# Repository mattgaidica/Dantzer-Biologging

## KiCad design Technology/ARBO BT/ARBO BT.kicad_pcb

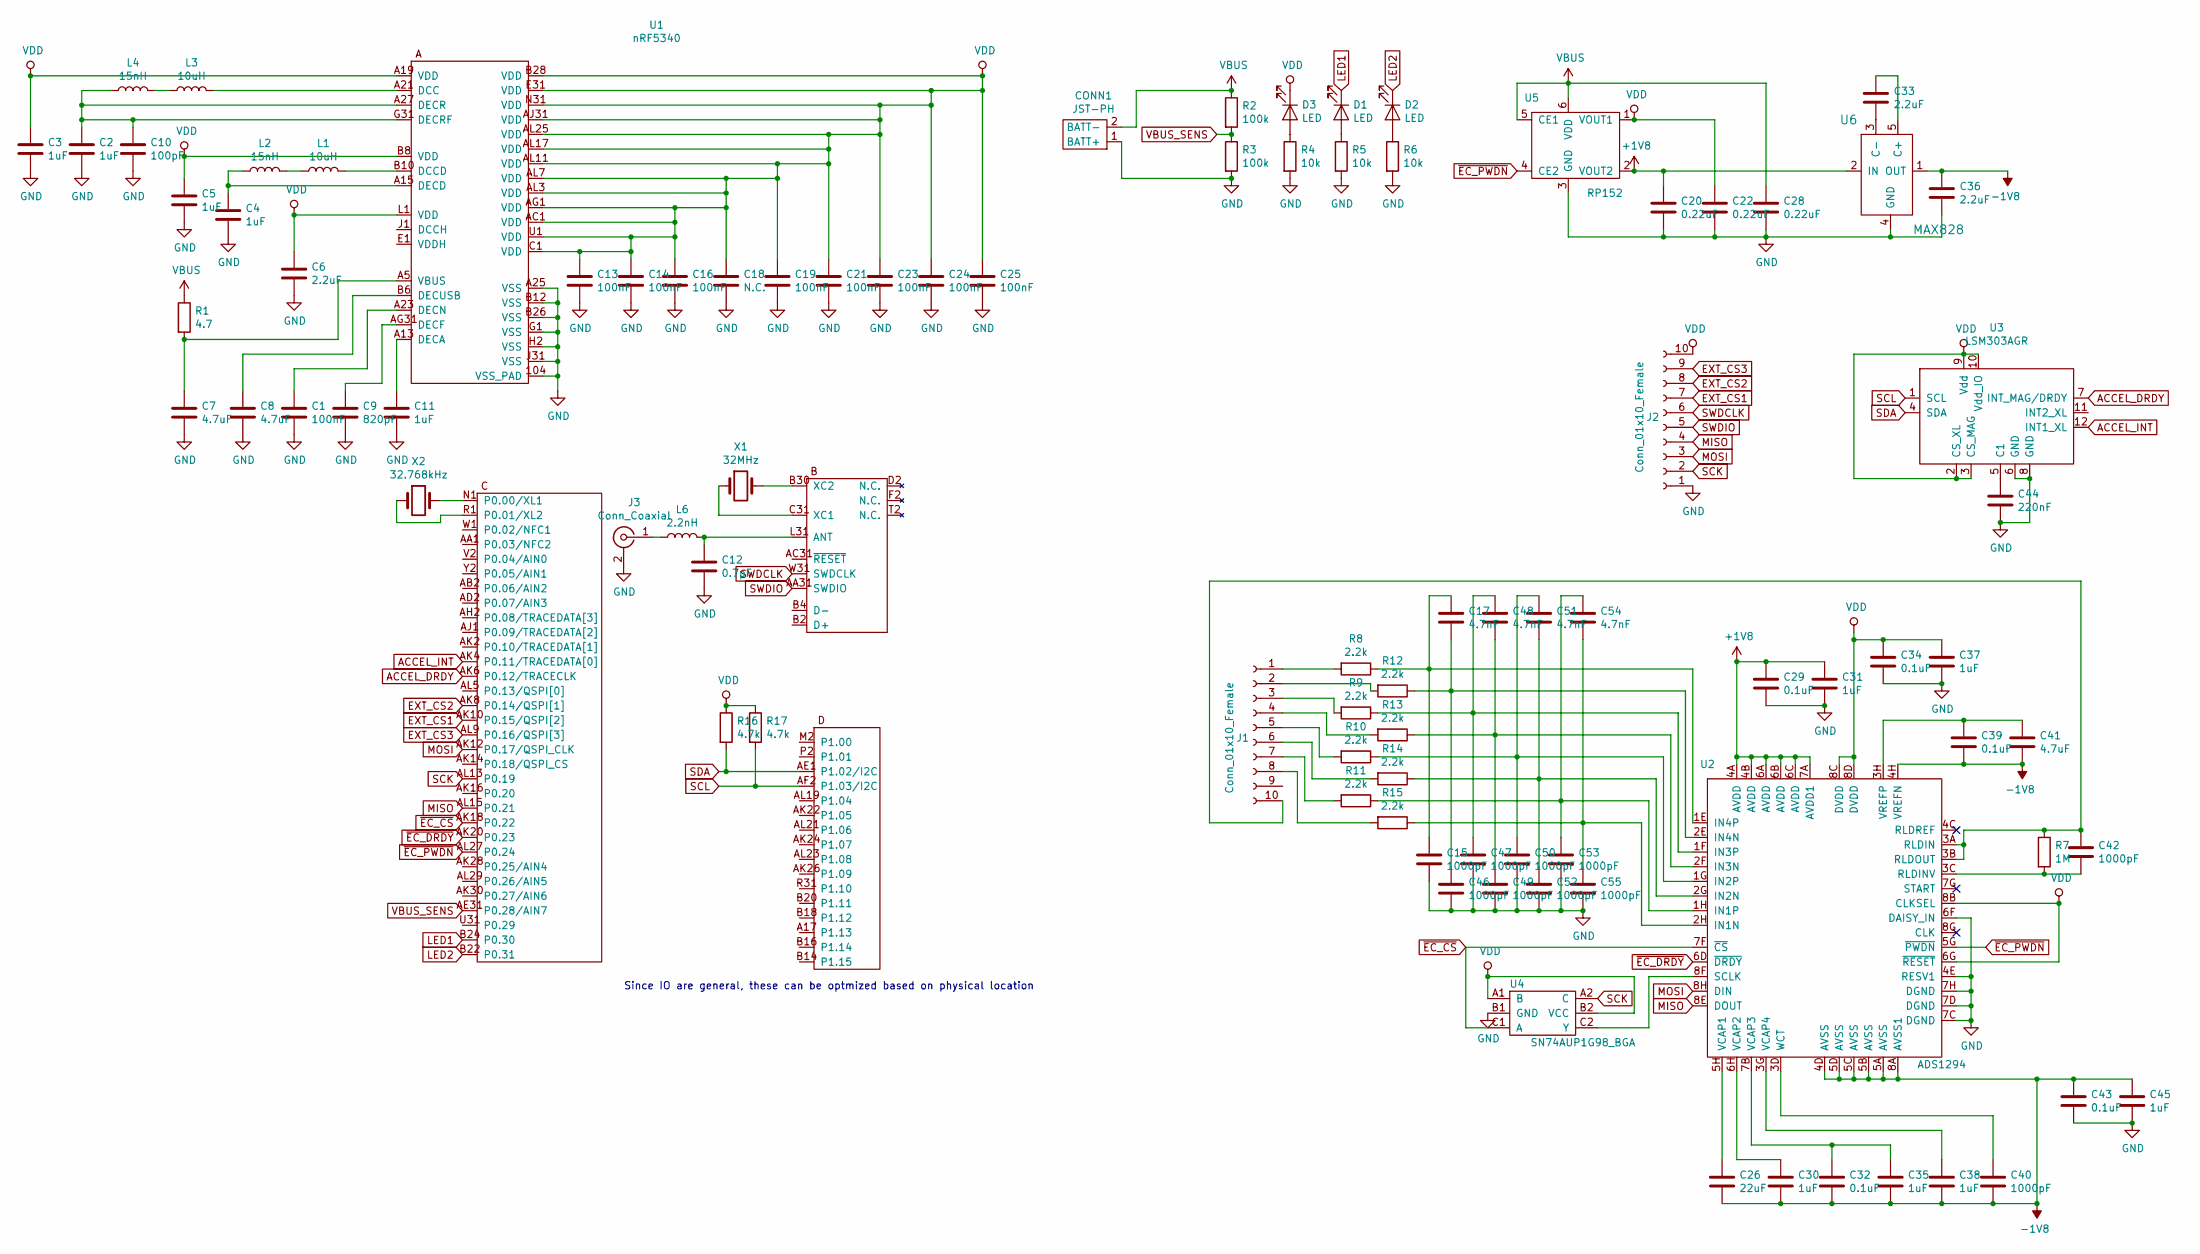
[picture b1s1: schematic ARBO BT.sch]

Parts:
C1, C13, C14, C16, C19, C21, C23, C24, C25: 100nF; C_0201_0603Metric
C2, C3, C4, C5, C11, C30, C31, C35, C37, C38, C45: 1uF; C_0402_1005Metric
C6, C33, C36: 2.2uF; C_0603_1608Metric
C7, C8, C41: 4.7uF; C_0603_1608Metric
C9: 820pF; C_0201_0603Metric
C10: 100pF; C_0201_0603Metric
C12: 0.7pF; C_0201_0603Metric
C15: 1000pF; C_0201_0603Metric
C17: 4.7nF; C_0201_0603Metric
C18: N.C.; C_0201_0603Metric
C20, C22, C28: 0.22uF; C_0402_1005Metric
C26: 22uF; C_0201_0603Metric
C29, C32, C34, C39, C43: 0.1uF; C_0201_0603Metric; digikey 490-16364-1-ND
C40, C42: 1000pF; C_0201_0603Metric; digikey 311-2073-1-ND
C44: 220nF; C_0402_1005Metric
C46, C47, C49, C50, C52, C53, C55: 1000pF; D_0201_0603Metric
C48, C51, C54: 4.7nF; D_0201_0603Metric
CONN1: JST-PH; JST_SHL_SM02B-SHLS-TF_1x02-1MP_P1.00mm_Horizontal
D1, D2, D3: LED; LED_0402_1005Metric
J1: Conn_01x10_Female; Hirose_DF52-10S-0.8H_1x10-1MP_P0.80mm_Horizontal
J2: Conn_01x10_Female; hirose_DF37NB-10
J3: Conn_Coaxial; U.FL_Hirose_U.FL-R-SMT-1_Vertical; digikey H9161CT-ND
L1, L3: 10uH; L_0603_1608Metric
L2, L4: 15nH; L_0201_0603Metric
L6: 2.2nH; L_0201_0603Metric
R1: 4.7; R_0201_0603Metric
R2, R3: 100k; R_0201_0603Metric
R4, R5, R6: 10k; R_0201_0603Metric
R7: 1M; R_0201_0603Metric
R8, R9, R10, R11, R12, R13, R14, R15: 2.2k; R_0201_0603Metric
R16, R17: 4.7k; R_0201_0603Metric
U1: nRF5340; aQFN94_7x7
U2: ADS1294; BGA-64_8x8_8.0x8.0mm_ADS129x
U3: LSM303AGR; LGA-12_2x2mm_P0.5mm
U4: SN74AUP1G98_BGA; BGA-6_04pitch
U5: RP152; digikey RP152L006B-TR
U6: MAX828; SOT-23-5
X1: 32MHz; Crystal_SMD_2016-4Pin_2.0x1.6mm
X2: 32.768kHz; Crystal_SMD_2012-2Pin_2.0x1.2mm

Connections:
+1V8: C20.1, C29.1, C31.1, U2.4A (AVDD), U2.4B (AVDD), U2.6A (AVDD), U2.6B (AVDD), U2.6C (AVDD), U2.7A (AVDD1), U5.2 (VOUT2), U6.2 (IN)
-1V8: C26.2, C30.2, C32.2, C35.2, C36.1, C38.2, C39.2, C40.2, C41.2, C43.1, C45.1, U2.4D (AVSS), U2.4H (VREFN), U2.5A (AVSS), U2.5B (AVSS), U2.5C (AVSS), U2.5D (AVSS), U2.8A (AVSS1), U6.1 (OUT)
ACCEL_DRDY: U1.AK6 (P0.12/TRACECLK), U3.7 (INT_MAG/DRDY)
ACCEL_INT: U1.AK4 (P0.11/TRACEDATA[0]), U3.12 (INT1_XL)
EXT_CS1: J2.7, U1.AK10 (P0.15/QSPI[2])
EXT_CS2: J2.8, U1.AK8 (P0.14/QSPI[1])
EXT_CS3: J2.9, U1.AL9 (P0.16/QSPI[3])
GND: C1.2, C2.2, C3.2, C4.2, C5.2, C6.2, C7.2, C8.2, C9.2, C10.2, C11.2, C12.2, C13.2, C14.2, C15.2, C16.2, C18.2, C19.2, C20.2, C21.2, C22.2, C23.2, C24.2, C25.2, C28.2, C29.2, C31.2, C34.2, C36.2, C37.2, C43.2, C44.2, C45.2, C46.2, C47.2, C49.2, C50.2, C52.2, C53.2, C55.2, CONN1.1 (BATT+), J2.1, J3.2 (Ext), R3.2, R4.2, R5.2, R6.2, U1.104 (VSS_PAD), U1.A25 (VSS), U1.B12 (VSS), U1.B26 (VSS), U1.G1 (VSS), U1.H2 (VSS), U1.J31 (VSS), U2.4E (RESV1), U2.6F (DAISY_IN), U2.7C (DGND), U2.7D (DGND), U2.7H (DGND), U3.6 (GND), U3.8 (GND), U4.B1 (GND), U5.3 (GND), U6.4 (GND)
LED1: D1.1 (K), U1.B24 (P0.30)
LED2: D2.1 (K), U1.B22 (P0.31)
MISO: J2.4, U1.AL15 (P0.21), U2.8E (DOUT)
MOSI: J2.3, U1.AK12 (P0.17/QSPI_CLK), U2.8H (DIN)
unnamed: C1.1, U1.A23 (DECN)
unnamed: C4.1, L2.1, U1.A15 (DECD)
unnamed: C7.1, R1.2, U1.A5 (VBUS)
unnamed: C8.1, U1.B6 (DECUSB)
unnamed: C9.1, U1.AG31 (DECF)
unnamed: C2.1, C10.1, L4.1, U1.A27 (DECR), U1.G31 (DECRF)
unnamed: C11.1, U1.A13 (DECA)
unnamed: C12.1, L6.2, U1.L31 (ANT)
unnamed: C15.1, C17.1, R8.1, U2.1E (IN4P)
unnamed: C17.2, C46.1, R12.1, U2.2E (IN4N)
unnamed: C26.1, U2.5H (VCAP1)
unnamed: C30.1, U2.6H (VCAP2)
unnamed: C32.1, C35.1, U2.7B (VCAP3)
unnamed: C33.1, U6.5 (C+)
unnamed: C33.2, U6.3 (C-)
unnamed: C38.1, U2.3G (VCAP4)
unnamed: C39.1, C41.1, U2.3H (VREFP)
unnamed: C40.1, U2.3D (WCT)
unnamed: C42.1, J1.10, R7.1, U2.3A (RLDIN), U2.3B (RLDOUT)
unnamed: C42.2, R7.2, U2.3C (RLDINV)
unnamed: C44.1, U3.5 (C1)
unnamed: C47.1, C48.1, R9.1, U2.1F (IN3P)
unnamed: C48.2, C49.1, R13.1, U2.2F (IN3N)
unnamed: C50.1, C51.1, R10.1, U2.1G (IN2P)
unnamed: C51.2, C52.1, R14.1, U2.2G (IN2N)
unnamed: C53.1, C54.1, R11.1, U2.1H (IN1P)
unnamed: C54.2, C55.1, R15.1, U2.2H (IN1N)
unnamed: D1.2 (A), R5.1
unnamed: D2.2 (A), R6.1
unnamed: D3.2 (A), R4.1
unnamed: J1.1, R8.2
unnamed: J1.2, R12.2
unnamed: J1.3, R9.2
unnamed: J1.4, R13.2
unnamed: J1.5, R10.2
unnamed: J1.6, R14.2
unnamed: J1.7, R11.2
unnamed: J1.8, R15.2
unnamed: J3.1 (In), L6.1
unnamed: L1.1, L2.2
unnamed: L1.2, U1.B10 (DCCD)
unnamed: L3.1, L4.2
unnamed: L3.2, U1.A21 (DCC)
unnamed: U1.B30 (XC2), X1.2
unnamed: U1.C31 (XC1), X1.1
unnamed: U1.N1 (P0.00/XL1), X2.2
unnamed: U1.R1 (P0.01/XL2), X2.1
unnamed: U2.8F (SCLK), U4.C2 (Y)
SCK: J2.2, U1.AL13 (P0.19), U4.A2 (C)
SCL: R17.2, U1.AF2 (P1.03/I2C), U3.1 (SCL)
SDA: R16.2, U1.AE1 (P1.02/I2C), U3.4 (SDA)
SWDCLK: J2.6, U1.W31 (SWDCLK)
SWDIO: J2.5, U1.AA31 (SWDIO)
VBUS: C28.1, CONN1.2 (BATT-), R1.1, R2.1, U5.5 (CE1), U5.6 (VDD)
VBUS_SENS: R2.2, R3.1, U1.AE31 (P0.28/AIN7)
VDD: C3.1, C5.1, C6.1, C13.1, C14.1, C16.1, C18.1, C19.1, C21.1, C22.1, C23.1, C24.1, C25.1, C34.1, C37.1, D3.1 (K), J2.10, R16.1, R17.1, U1.A19 (VDD), U1.AC1 (VDD), U1.AG1 (VDD), U1.AJ31 (VDD), U1.AL3 (VDD), U1.AL7 (VDD), U1.AL11 (VDD), U1.AL17 (VDD), U1.AL25 (VDD), U1.B8 (VDD), U1.B28 (VDD), U1.C1 (VDD), U1.E31 (VDD), U1.L1 (VDD), U1.N31 (VDD), U1.U1 (VDD), U2.6G (~RESET), U2.8B (CLKSEL), U2.8C (DVDD), U2.8D (DVDD), U3.2 (CS_XL), U3.3 (CS_MAG), U3.9 (Vdd), U3.10 (Vdd_IO), U4.A1 (B), U4.B2 (VCC), U5.1 (VOUT1)
~EC_CS: U1.AK18 (P0.22), U2.7F (~CS), U4.C1 (A)
~EC_DRDY: U1.AK20 (P0.23), U2.6D (~DRDY)
~EC_PWDN: U1.AL27 (P0.24), U2.5G (~PWDN), U5.4 (CE2)

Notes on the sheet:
Since IO are general, these can be optmized based on physical location

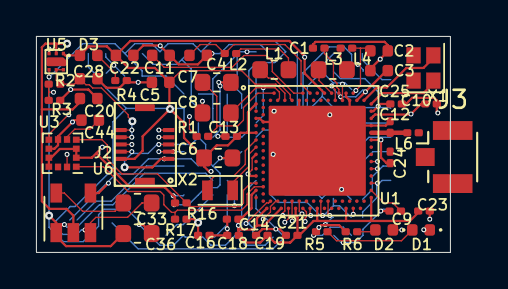
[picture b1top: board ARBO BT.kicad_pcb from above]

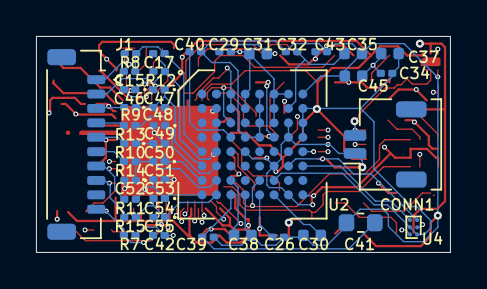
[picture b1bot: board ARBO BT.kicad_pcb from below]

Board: 4 copper layers, 23.0 x 12.0 mm, 91 parts (40 on the bottom side), 71 nets.

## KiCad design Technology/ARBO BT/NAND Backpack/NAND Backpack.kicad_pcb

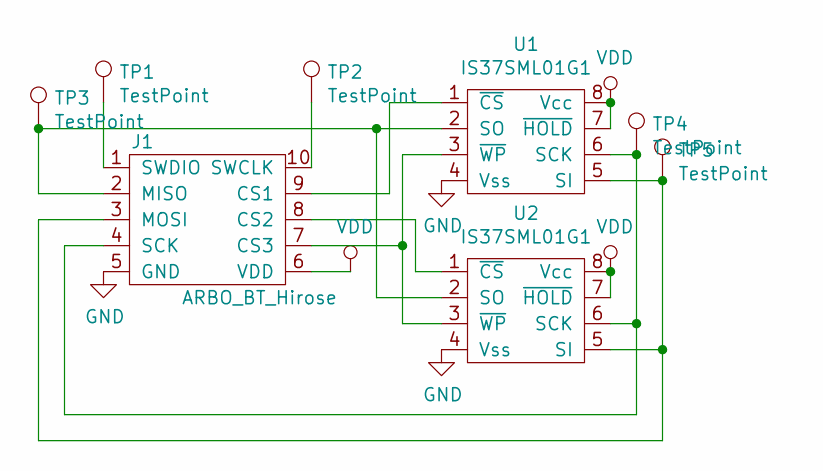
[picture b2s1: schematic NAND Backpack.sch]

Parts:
J1: ARBO_BT_Hirose; hirose_DF37B-10
TP1, TP2, TP3, TP4, TP5: TestPoint; TestPoint_Pad_D1.0mm
U1, U2: IS37SML01G1; 8x6mm_WSON_UTSO

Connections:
GND: J1.5 (GND), U1.4 (Vss), U2.4 (Vss)
unnamed: J1.1 (SWDIO), TP1.1
unnamed: J1.2 (MISO), TP3.1, U1.2 (SO), U2.2 (SO)
unnamed: J1.3 (MOSI), TP5.1, U1.5 (SI), U2.5 (SI)
unnamed: J1.4 (SCK), TP4.1, U1.6 (SCK), U2.6 (SCK)
unnamed: J1.7 (CS3), U1.3 (~WP), U2.3 (~WP)
unnamed: J1.8 (CS2), U2.1 (~CS)
unnamed: J1.9 (CS1), U1.1 (~CS)
unnamed: J1.10 (SWCLK), TP2.1
VDD: J1.6 (VDD), U1.7 (~HOLD), U1.8 (Vcc), U2.7 (~HOLD), U2.8 (Vcc)

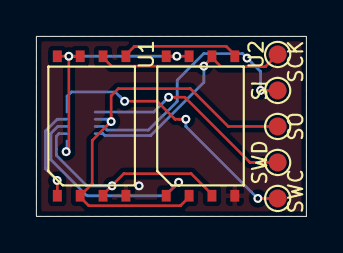
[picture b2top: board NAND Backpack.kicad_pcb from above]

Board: 2 copper layers, 15.0 x 10.0 mm, 8 parts (1 on the bottom side), 10 nets.

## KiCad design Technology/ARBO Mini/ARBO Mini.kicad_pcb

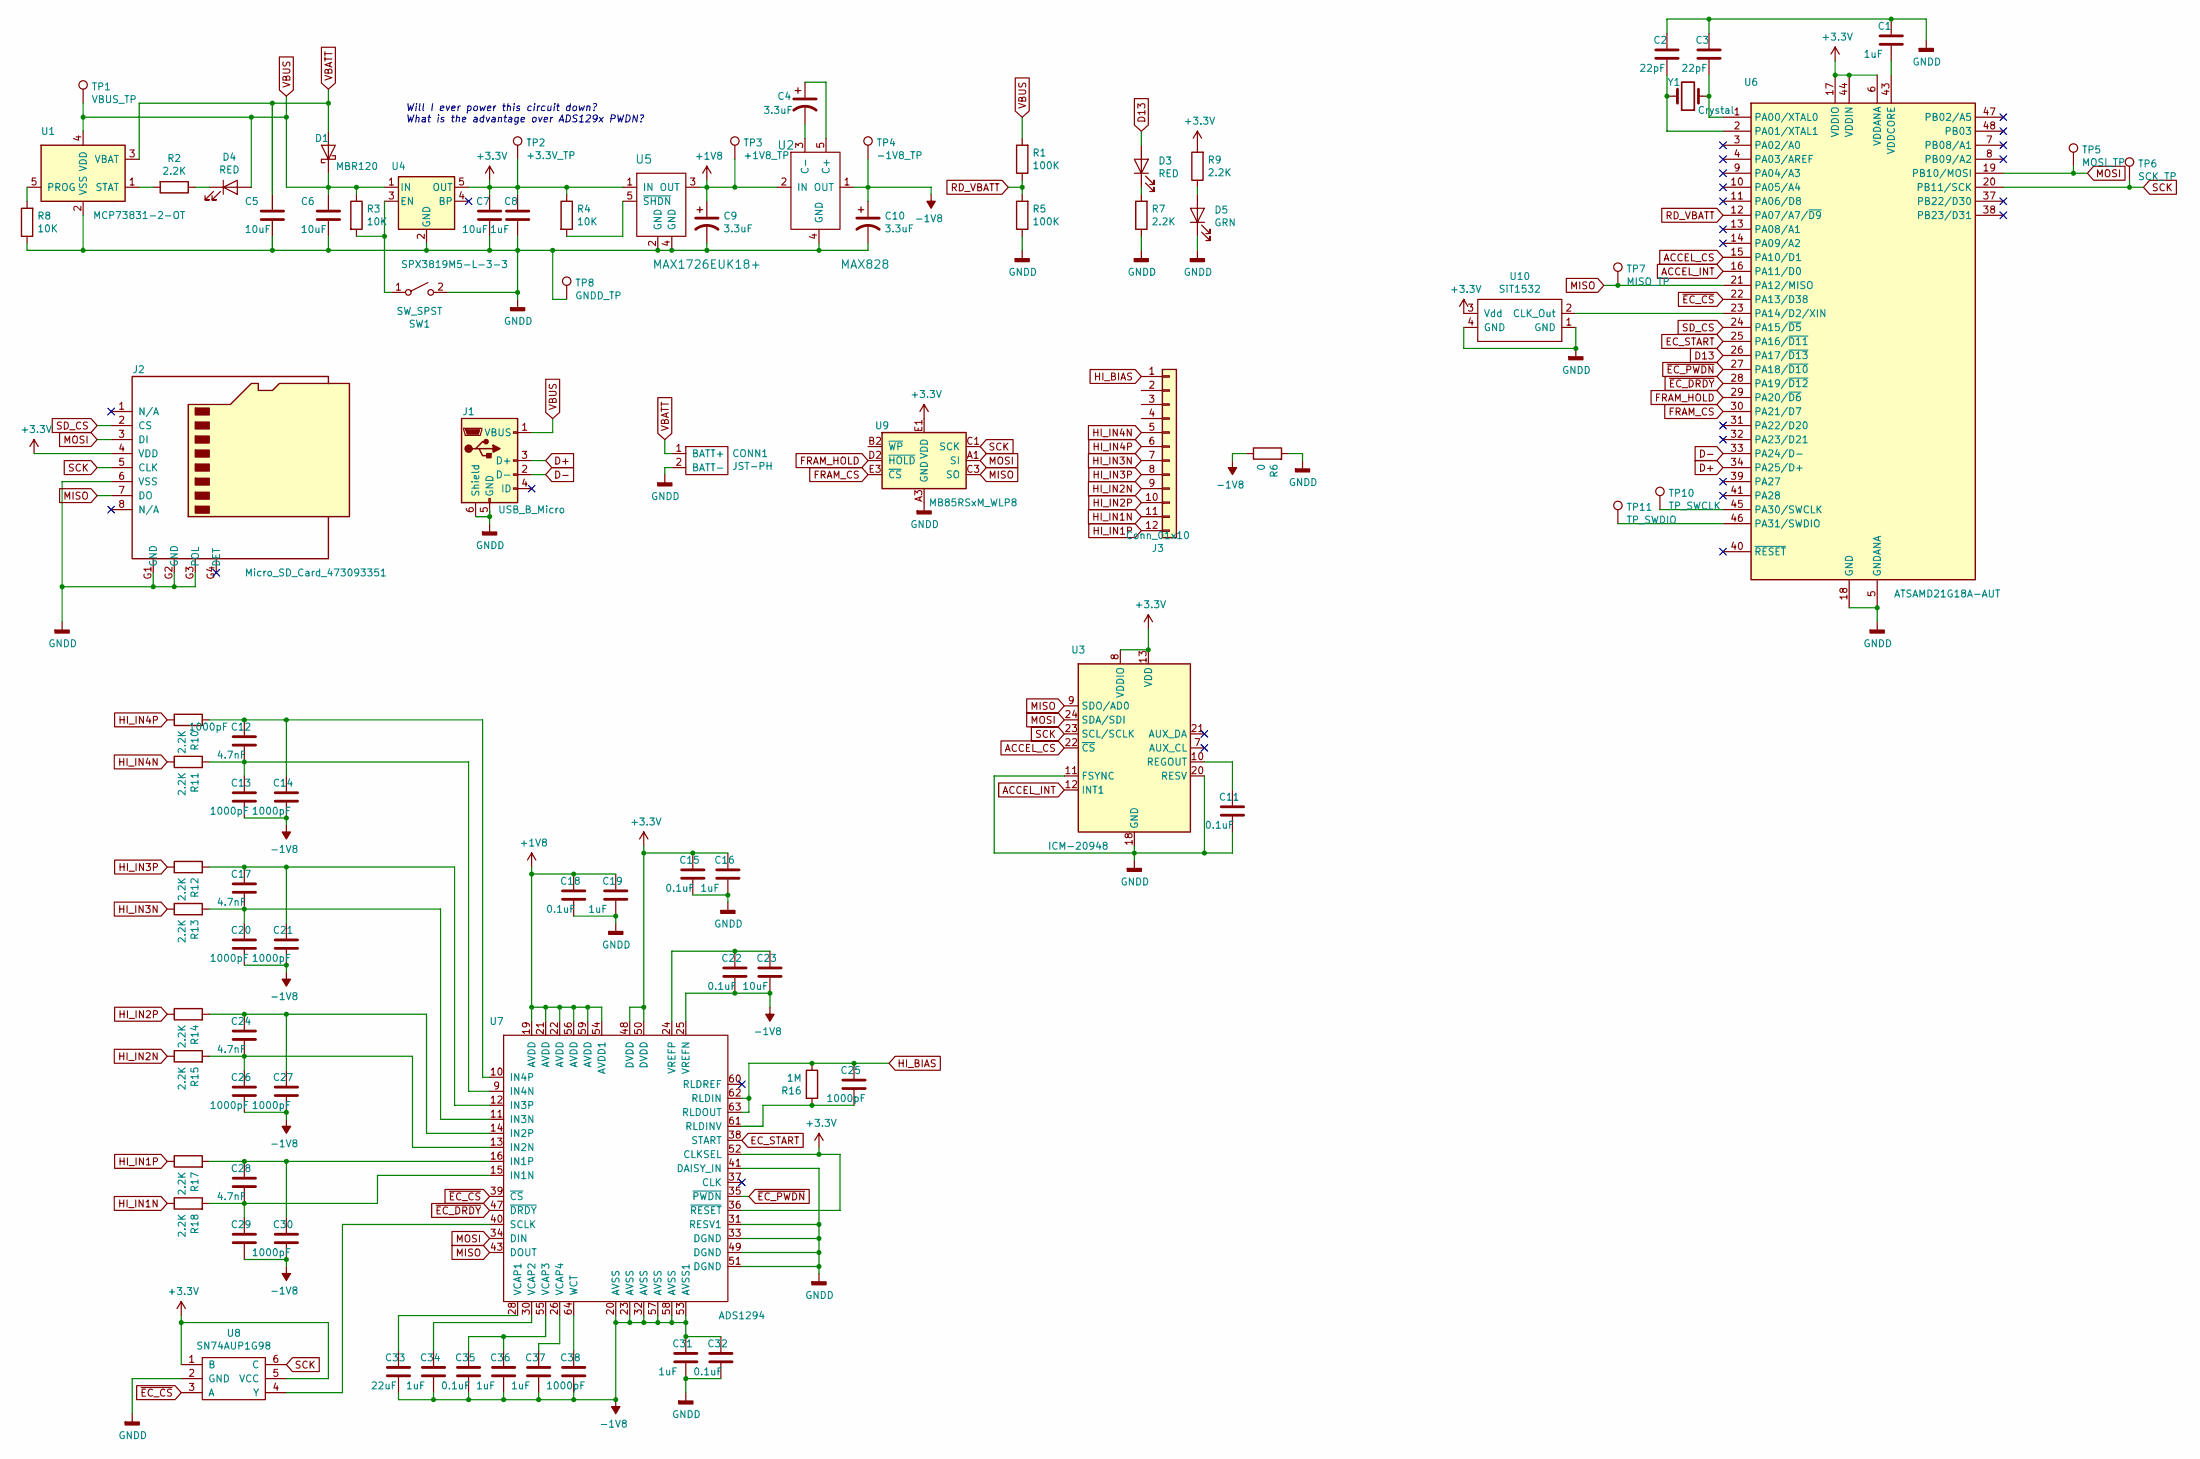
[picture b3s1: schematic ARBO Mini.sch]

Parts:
C1, C8, C16, C31, C34, C36, C37: 1uF; C_0402_1005Metric; Manufacturer Part Number C0402C105K9PACTU; Digi-key Part Number 399-4873-1-ND
C2, C3: 22pF; C_0402_1005Metric; Manufacturer Part Number C0402C220K5GACTU; Digi-key Part Number 399-7775-1-ND
C4, C9, C10: 3.3uF; C_0402_1005Metric; Manufacturer Part Number C1005X5R0G335K050BB; Digi-key Part Number 445-5948-1-ND
C5, C6, C7, C23: 10uF; C_0603_1608Metric; Manufacturer Part Number GRM155R60E106ME16D; Digi-key Part Number 490-10692-1-ND
C11, C15, C18, C22, C32, C35: 0.1uF; C_0402_1005Metric; Manufacturer Part Number LMK105BJ104KV-F; Digi-key Part Number 587-1227-1-ND
C12, C17, C24, C28: 4.7nF; C_0402_1005Metric; Manufacturer Part Number C0402C472K4RECAUTO; Digi-key Part Number 399-17875-1-ND
C13, C14, C20, C21, C25, C26, C27, C29, C30, C38: 1000pF; C_0402_1005Metric; Manufacturer Part Number GRM1555C1H102JA01J; Digi-key Part Number 490-6190-1-ND
C19: 1uF; C_0402_1005Metric; Manufacturer Part Number LMK105BJ104KV-F; Digi-key Part Number 587-1227-1-ND
C33: 22uF; C_0603_1608Metric; Manufacturer Part Number GRM188R60J226MEA0D; Digi-key Part Number 490-7611-1-ND
CONN1: JST-PH; PinHeader_1x02_P2.00mm_Horizontal
D1: MBR120; D_SOD-123F; Manufacturer Part Number MBR120VLSFT1G; Digi-key Part Number MBR120VLSFT1GOSCT-ND
D3, D4: RED; LED_0402_1005Metric; Manufacturer Part Number 150040RS73240; Digi-key Part Number 732-11991-1-ND
D5: GRN; LED_0402_1005Metric; Manufacturer Part Number 150040VS73240; Digi-key Part Number 732-11992-1-ND
J1: USB_B_Micro; USB_Micro-B_Molex-105017-0001; Manufacturer Part Number 1050170001; Digi-key Part Number WM1399CT-ND
J2: Micro_SD_Card_473093351; 473093351_uSDCard; Manufacturer Part Number 0473093351; Digi-key Part Number WM10795CT-ND
J3: Conn_01x10; Hirose_DF52-12S-0.8H_1x12-1MP_P0.80mm_Horizontal; Manufacturer Part Number DF52-12S-0.8H(21); Digi-key Part Number H125103CT-ND
R1, R5: 100K; R_0402_1005Metric; Manufacturer Part Number RC0402FR-07100KL; Digi-key Part Number 311-100KLRCT-ND
R2, R7, R9, R10, R11, R12, R13, R14, R15, R17, R18: 2.2K; R_0402_1005Metric; Manufacturer Part Number RC0402FR-072K2L; Digi-key Part Number 311-2.20KLRCT-ND
R3, R4, R8: 10K; R_0402_1005Metric; Manufacturer Part Number RC0402FR-0710KL; Digi-key Part Number 311-10.0KLRCT-ND
R6: 0; R_0402_1005Metric; Manufacturer Part Number RC0402JR-070RL; Digi-key Part Number 311-0.0JRCT-ND
R16: 1M; R_0402_1005Metric; Manufacturer Part Number RC0402FR-071ML; Digi-key Part Number 311-1.00MLRCT-ND
SW1: SW_SPST; SW_SPST_CK_KXT3; Manufacturer Part Number KXT 331 LHS; Digi-key Part Number CKN10779CT-ND
TP1: VBUS_TP; TestPoint_Pad_D1.5mm
TP2: +3.3V_TP; TestPoint_Pad_D1.5mm
TP3: +1V8_TP; TestPoint_Pad_D1.5mm
TP4: -1V8_TP; TestPoint_Pad_D1.5mm
TP5: MOSI_TP; TestPoint_Pad_D1.5mm
TP6: SCK_TP; TestPoint_Pad_D1.5mm
TP7: MISO_TP; TestPoint_Pad_D1.5mm
TP8: GNDD_TP; TestPoint_Pad_D1.5mm
TP10: TP_SWCLK; TestPoint_Pad_D1.5mm
TP11: TP_SWDIO; TestPoint_Pad_D1.5mm
U1: MCP73831-2-OT; SOT-23-5; Manufacturer Part Number MCP73831T-2ATI/OT; Digi-key Part Number MCP73831T-2ATI/OTCT-ND
U2: MAX828; SOT-23-5; Manufacturer Part Number MAX828EUK+T; Digi-key Part Number MAX828EUK+TCT-ND
U3: ICM-20948; InvenSense_QFN-24_3x3mm_P0.4mm; Manufacturer Part Number ICM-20948; Digi-key Part Number 1428-1123-1-ND
U4: SPX3819M5-L-3-3; SOT-23-5; Manufacturer Part Number SPX3819M5-L-3-3/TR; Digi-key Part Number 1016-1873-1-ND
U5: MAX1726EUK18+; SOT-23-5; Manufacturer Part Number MAX1726EUK18+T; Digi-key Part Number MAX1726EUK18+T-ND
U6: ATSAMD21G18A-AUT; QFN-48-1EP_7x7mm_P0.5mm_EP5.15x5.15mm; Manufacturer Part Number ATSAMD21G18A-MUT; Digi-key Part Number ATSAMD21G18A-MUTCT-ND
U7: ADS1294; TQFP-64-1EP_10x10mm_P0.5mm_EP8x8mm; Manufacturer Part Number ADS1294IPAG; Digi-key Part Number 296-27932-ND
U8: SN74AUP1G98; SOT-23-6; Manufacturer Part Number SN74AUP1G98DBVR; Digi-key Part Number 296-19087-1-ND
U9: MB85RSxM_WLP8; BGA8CP30X40_5X3_309X228X35B25N; Manufacturer Part Number MB85RS1MTPW-G-APEWE1; Digi-key Part Number 865-1272-2-ND
U10: SiT1532; Manufacturer Part Number SIT1532AI-J4-DCC-32.768E; Digi-key Part Number 1473-1240-1-ND
Y1: Crystal; Crystal_SMD_3215-2Pin_3.2x1.5mm; Manufacturer Part Number FC-135 32.7680KA-A5; Digi-key Part Number SER4103CT-ND

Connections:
+1V8: C9.1, C18.1, C19.1, TP3.1, U2.2 (IN), U5.3 (OUT), U7.19 (AVDD), U7.21 (AVDD), U7.22 (AVDD), U7.54 (AVDD1), U7.56 (AVDD), U7.59 (AVDD)
+3V3: C7.1, C8.1, C15.1, C16.1, J2.4 (VDD), R4.1, R9.2, TP2.1, U3.8 (VDDIO), U3.13 (VDD), U4.5 (OUT), U5.1 (IN), U6.6 (VDDANA), U6.17 (VDDIO), U6.36 (VDDIO), U6.44 (VDDIN), U7.36 (~RESET), U7.48 (DVDD), U7.50 (DVDD), U7.52 (CLKSEL), U8.1 (B), U8.5 (VCC), U9.E1 (VDD), U10.3 (Vdd)
-1V8: C10.1, C13.2, C14.2, C20.2, C21.2, C22.2, C23.2, C26.2, C27.2, C29.2, C30.2, C31.1, C32.1, C33.2, C34.2, C35.2, C36.2, C37.2, C38.2, R6.1, TP4.1, U2.1 (OUT), U7.20 (AVSS), U7.23 (AVSS), U7.25 (VREFN), U7.32 (AVSS), U7.53 (AVSS1), U7.57 (AVSS), U7.58 (AVSS)
ACCEL_CS: U3.22 (~CS), U6.15 (PA10/D1)
ACCEL_INT: U3.12 (INT1), U6.16 (PA11/D0)
D13: D3.2 (A), U6.26 (PA17/~D13)
D+: J1.3 (D+), U6.34 (PA25/D+)
D-: J1.2 (D-), U6.33 (PA24/D-)
EC_START: U6.25 (PA16/~D11), U7.38 (START)
FRAM_CS: U6.30 (PA21/D7), U9.E3 (~CS)
FRAM_HOLD: U6.29 (PA20/~D6), U9.D2 (~HOLD)
GNDD: C1.1, C2.1, C3.1, C5.2, C6.2, C7.2, C8.2, C9.2, C10.2, C11.2, C15.2, C16.2, C18.2, C19.2, C31.2, C32.2, CONN1.2 (BATT-), D5.1 (K), J1.5 (GND), J1.6 (Shield), J2.6 (VSS), J2.G1 (GND), J2.G2 (GND), J2.G3 (POL), R5.1, R6.2, R7.1, R8.1, SW1.2 (B), TP8.1, U1.2 (VSS), U2.4 (GND), U3.11 (FSYNC), U3.18 (GND), U3.20 (GND), U4.2 (GND), U5.2 (GND), U5.4 (GND), U6.5 (GNDANA), U6.18 (GND), U6.35 (GND), U6.42 (GND), U7.31 (RESV1), U7.33 (DGND), U7.41 (DAISY_IN), U7.49 (DGND), U7.51 (DGND), U8.2 (GND), U9.A3 (GND), U10.1 (GND), U10.4 (GND)
HI_BIAS: C25.1, J3.1, R16.1, U7.62 (RLDIN), U7.63 (RLDOUT)
HI_IN1N: J3.11, R18.1
HI_IN1P: J3.12, R17.1
HI_IN2N: J3.9, R15.1
HI_IN2P: J3.10, R14.1
HI_IN3N: J3.7, R13.1
HI_IN3P: J3.8, R12.1
HI_IN4N: J3.5, R11.1
HI_IN4P: J3.6, R10.1
MISO: J2.7 (DO), TP7.1, U3.9 (SDO/AD0), U6.21 (PA12/MISO), U7.43 (DOUT), U9.C3 (SO)
MOSI: J2.3 (DI), TP5.1, U3.24 (SDA/SDI), U6.19 (PB10/MOSI), U7.34 (DIN), U9.A1 (SI)
unnamed: C1.2, U6.43 (VDDCORE)
unnamed: C2.2, U6.2 (PA01/XTAL1), Y1.2
unnamed: C3.2, U6.1 (PA00/XTAL0), Y1.1
unnamed: C4.1, U2.5 (C+)
unnamed: C4.2, U2.3 (C-)
unnamed: C11.1, U3.10 (REGOUT)
unnamed: C12.1, C14.1, R10.2, U7.10 (IN4P)
unnamed: C12.2, C13.1, R11.2, U7.9 (IN4N)
unnamed: C17.1, C21.1, R12.2, U7.12 (IN3P)
unnamed: C17.2, C20.1, R13.2, U7.11 (IN3N)
unnamed: C22.1, C23.1, U7.24 (VREFP)
unnamed: C24.1, C27.1, R14.2, U7.14 (IN2P)
unnamed: C24.2, C26.1, R15.2, U7.13 (IN2N)
unnamed: C25.2, R16.2, U7.61 (RLDINV)
unnamed: C28.1, C30.1, R17.2, U7.16 (IN1P)
unnamed: C28.2, C29.1, R18.2, U7.15 (IN1N)
unnamed: C33.1, U7.28 (VCAP1)
unnamed: C34.1, U7.30 (VCAP2)
unnamed: C35.1, C36.1, U7.55 (VCAP3)
unnamed: C37.1, U7.26 (VCAP4)
unnamed: C38.1, U7.64 (WCT)
unnamed: D3.1 (K), R7.2
unnamed: D4.1 (K), R2.1
unnamed: D5.2 (A), R9.1
unnamed: R2.2, U1.1 (STAT)
unnamed: R3.2, SW1.1 (A), U4.3 (EN)
unnamed: R4.2, U5.5 (~SHDN)
unnamed: R8.2, U1.5 (PROG)
unnamed: TP10.1, U6.45 (PA30/SWCLK)
unnamed: TP11.1, U6.46 (PA31/SWDIO)
unnamed: U7.40 (SCLK), U8.4 (Y)
unnamed: U6.23 (PA14/D2/XIN), U10.2 (CLK_Out)
RD_VBATT: R1.1, R5.2, U6.12 (PA07/A7/~D9)
SCK: J2.5 (CLK), TP6.1, U3.23 (SCL/SCLK), U6.20 (PB11/SCK), U8.6 (C), U9.C1 (SCK)
SD_CS: J2.2 (CS), U6.24 (PA15/~D5)
VBATT: C5.1, CONN1.1 (BATT+), D1.2 (A), U1.3 (VBAT)
VBUS: C6.1, D1.1 (K), D4.2 (A), J1.1 (VBUS), R1.2, R3.1, TP1.1, U1.4 (VDD), U4.1 (IN)
~EC_CS: U6.22 (PA13/D38), U7.39 (~CS), U8.3 (A)
~EC_DRDY: U6.28 (PA19/~D12), U7.47 (~DRDY)
~EC_PWDN: U6.27 (PA18/~D10), U7.35 (~PWDN)

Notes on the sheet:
Will I ever power this circuit down? What is the advantage over ADS129x PWDN?

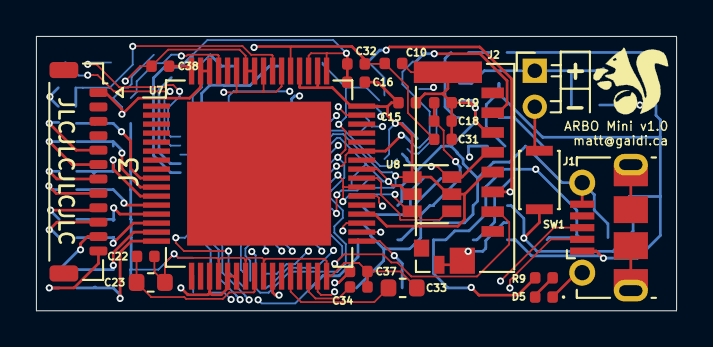
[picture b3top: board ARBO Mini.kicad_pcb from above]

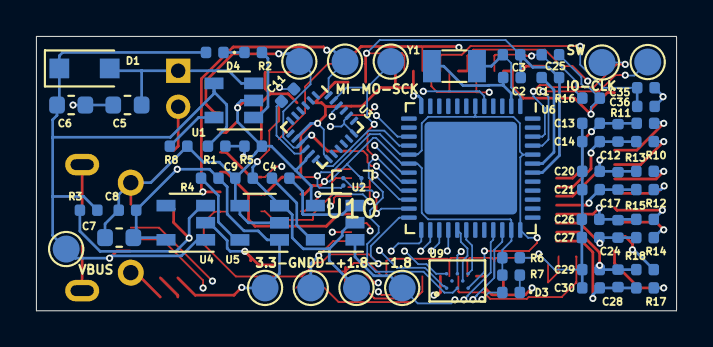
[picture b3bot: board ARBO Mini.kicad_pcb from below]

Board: 4 copper layers, 35.6 x 15.2 mm, 86 parts (64 on the bottom side), 63 nets.

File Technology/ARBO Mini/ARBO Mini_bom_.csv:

Component,Description,Part,References,Value,Footprint,Quantity Per PCB,Datasheet,Manufacturer Part Number,Digi-key Part Number,Link
1,Unpolarized capacitor,C,C11 C15 C18 C19 C22 C32 C35,0.1uF,C_0402_1005Metric,7,~,LMK105BJ104KV-F,587-1227-1-ND,
2,Unpolarized capacitor,C,C13 C14 C20 C21 C25 C26 C27 C29 C30 C38,1000pF,C_0402_1005Metric,10,~,GRM1555C1H102JA01J,490-6190-1-ND,
3,Unpolarized capacitor,C,C5 C6 C7 C23,10uF,C_0603_1608Metric,4,~,GRM155R60E106ME16D,490-10692-1-ND,
4,Unpolarized capacitor,C,C1 C8 C16 C31 C34 C36 C37,1uF,C_0402_1005Metric,7,~,C0402C105K9PACTU,399-4873-1-ND,
5,Unpolarized capacitor,C,C2 C3,22pF,C_0402_1005Metric,2,~,C0402C105K9PACTU,399-4873-1-ND,
6,Unpolarized capacitor,C,C33,22uF,C_0603_1608Metric,1,~,GRM188R60J226MEA0D,490-7611-1-ND,
7,"Polarized capacitor, US symbol",CP1,C4 C9 C10,3.3uF,C_0402_1005Metric,3,~,C1005X5R0G335K050BB,445-5948-1-ND,
8,Unpolarized capacitor,C,C12 C17 C24 C28,4.7nF,C_0402_1005Metric,4,~,C0402C472K4RECAUTO,399-17875-1-ND,
9,,JST-PH,CONN1,JST-PH,PinHeader_1x02_P2.00mm_Horizontal,1,,,,
10,Light emitting diode,LED,D5,GRN,LED_0402_1005Metric,1,~,150040VS73240,732-11992-1-ND,
11,Schottky diode,D_Schottky,D1,MBR120,D_SOD-123F,1,https://www.digikey.com/product-detail/en/on-semiconductor/M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,MBR120VLSFT1G,MBR120VLSFT1GOSCT-ND,
12,Light emitting diode,LED,D3 D4,RED,LED_0402_1005Metric,2,~,150040RS73240,732-11991-1-ND,
13,"Generic connector, single row, 01x12, script generated (kicad-library-utils/schlib/autogen/connector/)",Conn_01x12,J3,Conn_01x10,Hirose_DF52-12S-0.8H_1x12-1MP_P0.80mm_Horizontal,1,~,DF52-12S-0.8H(21),H125103CT-ND,
14,Micro SD Card Socket with card detection pins,Micro_SD_Card_473093351,J2,Micro_SD_Card_473093351,473093351_uSDCard,1,https://www.hirose.com/product/en/download_file/key_name/DM3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,0473093351,WM10795CT-ND,
15,USB Micro Type B connector,USB_B_Micro,J1,USB_B_Micro,USB_Micro-B_Molex-105017-0001,1,~,1050170001,WM1399CT-ND,
16,Resistor,R,R6,0,R_0402_1005Metric,1,~,RC0402JR-070RL,311-0.0JRCT-ND,
17,Resistor,R,R1 R5,100K,R_0402_1005Metric,2,~,RC0402FR-07100KL,311-100KLRCT-ND,
18,Resistor,R,R3 R4 R8,10K,R_0402_1005Metric,3,~,RC0402FR-0710KL,311-10.0KLRCT-ND,
19,Resistor,R,R16,1M,R_0402_1005Metric,1,~,RC0402FR-071ML,311-1.00MLRCT-ND,
20,Resistor,R,R2 R7 R9 R10 R11 R12 R13 R14 R15 R17 R18,2.2K,R_0402_1005Metric,11,~,RC0402FR-072K2L,311-2.20KLRCT-ND,
21,Single Pole Single Throw (SPST) switch,SW_SPST,SW1,SW_SPST,SW_SPST_CK_KXT3,1,~,KXT 331 LHS,CKN10779CT-ND,
22,,ADS1294_TQFP,U7,ADS1294,TQFP-64-1EP_10x10mm_P0.5mm_EP8x8mm,1,,ADS1294IPAG,296-27932-ND,
23,"SAM D21 Microchip SMART ARM-based Flash MCU, 48Mhz, 256K Flash, 32K SRAM, TQFP-48",ATSAMD21G18A-AUT,U6,ATSAMD21G18A-AUT,QFN-48-1EP_7x7mm_P0.5mm_EP5.15x5.15mm,1,http://ww1.microchip.com/downloads/en/DeviceDoc/SAMD21-Famil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,ATSAMD21G18A-MUT,ATSAMD21G18A-MUTCT-ND,https://www.digikey.com/product-detail/en/microchip-technolo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
24,"InvenSense 9-Axis Motion Sensor, Accelerometer, Gyroscope, Compass, I2C/SPI, QFN-24",ICM-20948,U3,ICM-20948,InvenSense_QFN-24_3x3mm_P0.4mm,1,http://www.invensense.com/wp-content/uploads/2016/06/DS-0001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,ICM-20948,1428-1123-1-ND,
25,,MAX1726EUK18+,U5,MAX1726EUK18+,SOT-23-5,1,,MAX1726EUK18+T,MAX1726EUK18+T-ND,
26,,MAX828,U2,MAX828,SOT-23-5,1,,MAX828EUK+T,MAX828EUK+TCT-ND,
27,"FRAM memory with SPI interface, SOIC-8 SON-8",MB85RSxM_WLP8,U9,MB85RSxM_WLP8,BGA8CP30X40_5X3_309X228X35B25N,1,http://www.fujitsu.com/downloads/MICRO/fsa/pdf/products/memo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,MB85RS1MTPW-G-APEWE1,865-1272-2-ND,
28,"Single cell, Li-Ion/Li-Po charge management controller, 4.20V, Tri-State Status Output, in SOT23-5 package",MCP73831-2-OT,U1,MCP73831-2-OT,SOT-23-5,1,http://ww1.microchip.com/downloads/en/DeviceDoc/20001984g.pdf,MCP73831T-2ATI/OT,MCP73831T-2ATI/OTCT-ND,
29,,SN74AUP1G98,U8,SN74AUP1G98,SOT-23-6,1,,SN74AUP1G98DBVR,296-19087-1-ND,
30,"500mA Low drop-out regulator, Fixed Output 3.3V, SOT-23-5",SPX3819M5-L-3-3,U4,SPX3819M5-L-3-3,SOT-23-5,1,https://www.exar.com/content/document.ashx?id=22106&language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,SPX3819M5-L-3-3/TR,1016-1873-1-ND,
31,,SiT1532,U10,SiT1532,SiT1532,1,,SIT1532AI-J4-DCC-32.768E,1473-1240-1-ND,
32,Two pin crystal,Crystal,Y1,Crystal,Crystal_SMD_3215-2Pin_3.2x1.5mm,1,~,FC-135 32.7680KA-A5,SER4103CT-ND,





Component Groups:,32
Component Count:,76
Fitted Components:,76
Number of PCBs:,1
Total components:,76
Schematic Version:,
Schematic Date:,
BoM Date:,"Wednesday, January 08, 2020 at 03:53:28 PM"
Schematic Source:,/Users/matt/Box Sync/Biologging/Technology/ARBO Mini/ARBO Mini.sch
KiCad Version:,Eeschema (5.1.2-1)-1
